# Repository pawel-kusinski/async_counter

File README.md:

# 4-Bit J-K Flip-Flop Asynchronous (Ripple) Counter

An asynchronous counter built with J-K Flip-Flops, designed on a small PCB module suitable for breadboard circuits.

## Design Files

The board was created using KiCad, and the project files can be found in the `KiCad` directory. If you prefer to view the schematic without KiCad, a PDF version is available in the `schematic_pdf` directory.

## Gerber Files

All the necessary files for PCB fabrication are stored in the `fabrication_outputs` directory.

## Logisim Simulation

To see how the circuit works in a simulation, you can check the Logisim-evolution project file, which is available in the `Logisim` directory.

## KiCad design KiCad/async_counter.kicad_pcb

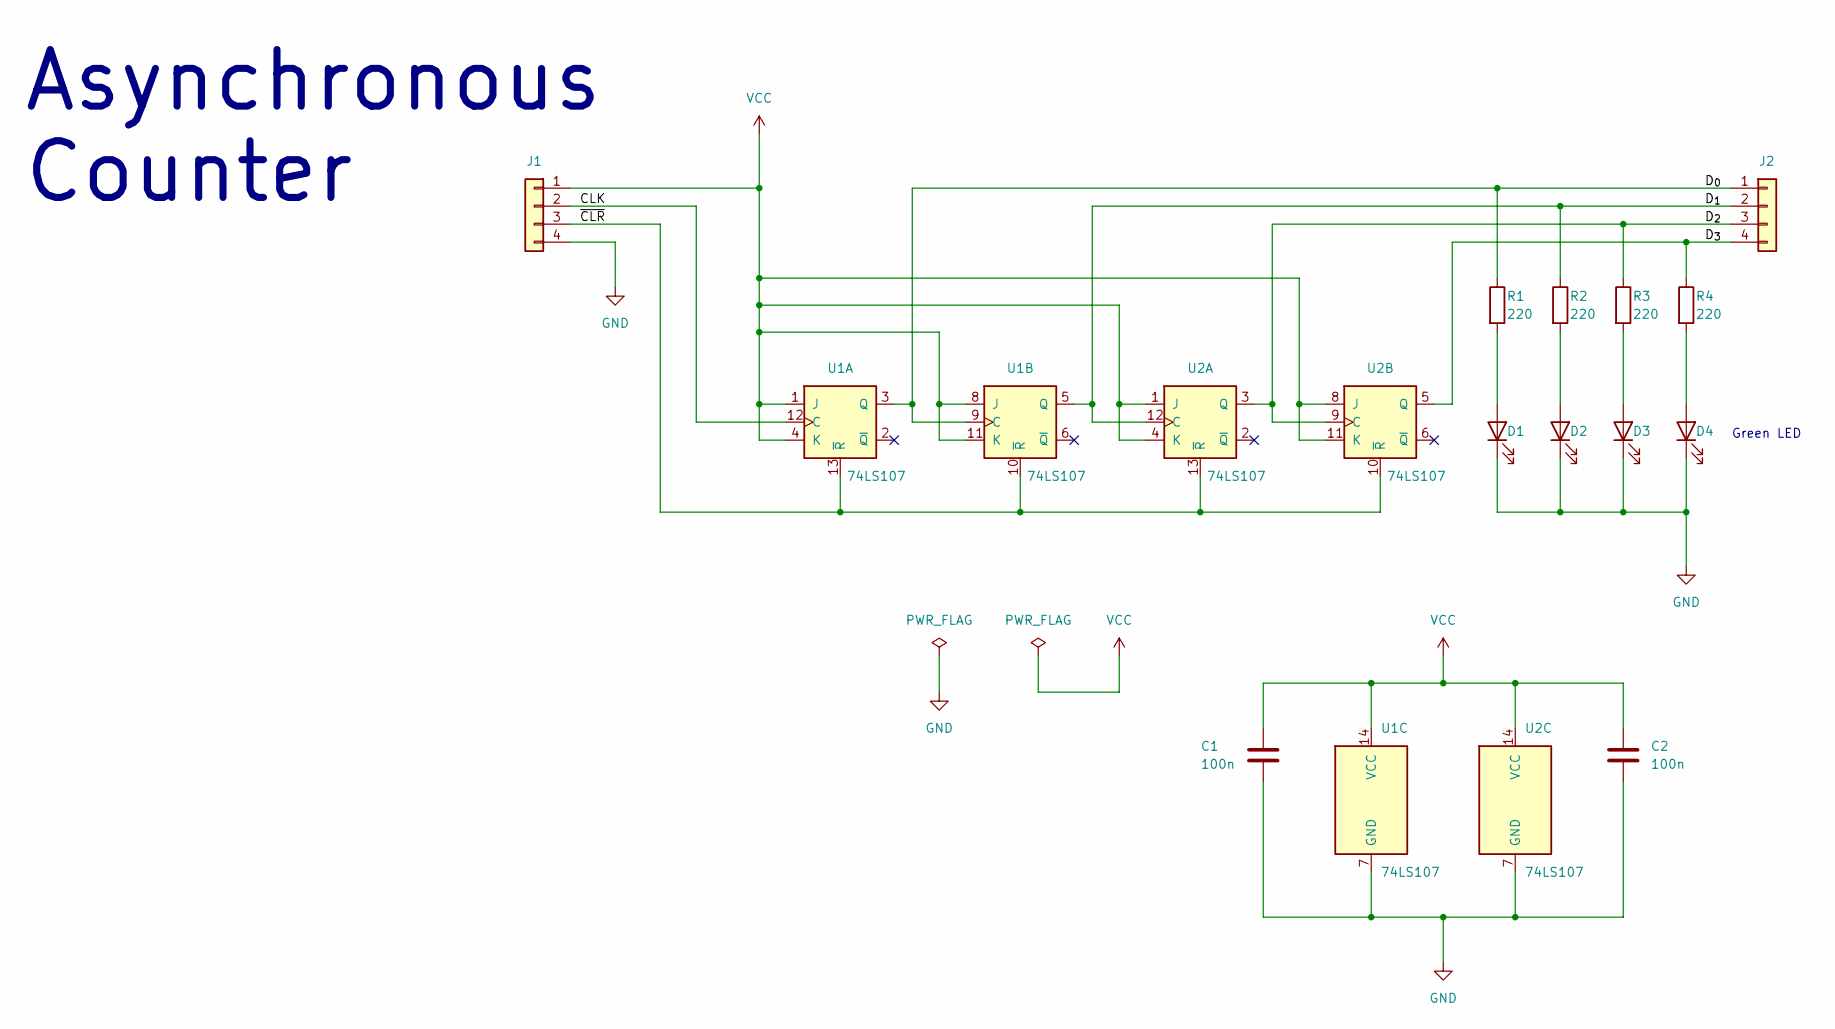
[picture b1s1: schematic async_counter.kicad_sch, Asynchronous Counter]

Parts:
C1, C2: 100n; C_0805_2012Metric_Pad1.18x1.45mm_HandSolder
D1, D2, D3, D4: LED; LED_0805_2012Metric_Pad1.15x1.40mm_HandSolder
J1, J2: Conn_01x04; PinHeader_1x04_P2.54mm_Vertical
R1, R2, R3, R4: 220; R_0805_2012Metric_Pad1.20x1.40mm_HandSolder
U1, U2: 74LS107; DIP-14_W7.62mm

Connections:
/CLK: J1.2, U1.12 (C)
/D_{0}: J2.1, R1.1, U1.3 (Q), U1.9 (C)
/D_{1}: J2.2, R2.1, U1.5 (Q), U2.12 (C)
/D_{2}: J2.3, R3.1, U2.3 (Q), U2.9 (C)
/D_{3}: J2.4, R4.1, U2.5 (Q)
/~CLR: J1.3, U1.10 (~R), U1.13 (~R), U2.10 (~R), U2.13 (~R)
GND: C1.2, C2.2, D1.1 (K), D2.1 (K), D3.1 (K), D4.1 (K), J1.4, U1.7 (GND), U2.7 (GND)
unnamed: D1.2 (A), R1.2
unnamed: D2.2 (A), R2.2
unnamed: D3.2 (A), R3.2
unnamed: D4.2 (A), R4.2
VCC: C1.1, C2.1, J1.1, U1.1 (J), U1.4 (K), U1.8 (J), U1.11 (K), U1.14 (VCC), U2.1 (J), U2.4 (K), U2.8 (J), U2.11 (K), U2.14 (VCC)

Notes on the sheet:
Green LED
Asynchronous Counter

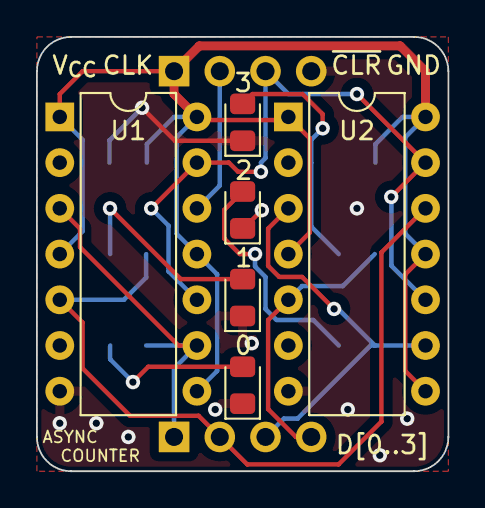
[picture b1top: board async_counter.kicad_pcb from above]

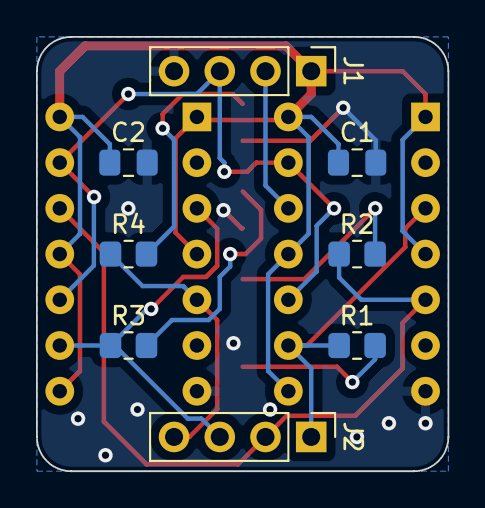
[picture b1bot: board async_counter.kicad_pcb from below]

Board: 2 copper layers, 22.9 x 24.1 mm, 14 parts (8 on the bottom side), 12 nets.
